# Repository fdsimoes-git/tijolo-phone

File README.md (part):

# Tijolo — dumbphone com ESP32-S3 e 4G

Celular "tijolinho" montado na **LILYGO T-A7670SA-S3-Standard**: ESP32-S3 + modem SIMCom A7670SA (4G Cat-1 + 2G) na mesma placa, com suporte para 18650, amplificador de áudio e conectores para alto-falante e microfone.

O firmware é o **TijoloOS**, feito por fases:

| Fase | O que entra | Situação |
|---|---|---|
| 1 | Modem: ligar, atender, SMS com acentos, USSD (saldo), toque — pelo Monitor Serial | pronta, testada na placa |
| 2 | Tela ILI9341 + teclado 3×4 (o 1 e o 3, segurados, fazem as vezes dos botões verde e vermelho): tela inicial, discador, chamadas, SMS recebidos, saldo, liga/desliga | pronta, testada na placa |
| 3a | Menu, escrever SMS pelo teclado (multitoque), caixa de mensagens na memória do Tijolo (ler, responder, encaminhar, apagar, reenviar) | pronta, testada na placa |
| 4 | **WhatsApp pela ponte**: um Android em casa, com o WhatsApp oficial, repassa as mensagens por SMS e devolve as respostas (app em [`ponte-android/`](ponte-android/README.md)) | pronta, falta testar na placa |
| 4 | **Montagem final**: PCB da frente encaixada nos pinos da LILYGO, sem fios soltos, e caixa impressa em 3D ([`montagem/`](montagem/README.md)) | desenhada e conferida no computador, já com as medidas das peças do Felipe; falta encomendar a PCB, imprimir a caixa e montar |
| 3b | Agenda de contatos (na memória do Tijolo), histórico de chamadas, despertador | depois |
| — | Modo roteador (compartilhar o 4G por Wi-Fi) | opcional |

O Monitor Serial continua aceitando todos os comandos da Fase 1.

## Peças

- LILYGO T-A7670SA-S3-Standard, versão **Without GPS** (modem A7670SA-LASE), com antena LTE, chip nano-SIM e uma 18650
- Alto-falante 3525 de 8 Ω, microfone de eletreto 9×7 mm e dois cabos JST SH 1.0 de 2 pinos (Fase 1)
- Tela TFT de 2,4" SPI com ILI9341 (240×320, sem touch)
- Teclado matricial 3×4 (12 teclas, 7 fios)
- Protoboard e jumpers (os 2 botões de pressão do kit Eletrogate são opcionais: sem eles, o 1 e o 3 seguradas fazem o papel deles)
- Para a montagem final: a PCB da frente (encomendada), duas barras fêmea de perna longa, fita dupla face de espuma e a caixa impressa em 3D (a lista completa está no guia de montagem; veja [Montagem final](#montagem-final-pcb-e-caixa))

## Montagem da Fase 1 (modem e áudio)

1. **Antena primeiro.** Nunca ligue o modem sem antena: transmitindo "no vazio", o amplificador de rádio dele pode queimar.
2. **Chip com a placa desligada.** Se o chip entrar com a placa ligada, o modem não o enxerga até reiniciar.
3. **Alto-falante → conector `SPEK`.** O alto-falante vem com um conector JST de 1,25 mm, que não serve: corte, emende os dois fios num cabo SH 1.0 (solda + termo-retrátil) e encaixe. A polaridade não importa para funcionar. Nunca ligue um fio do alto-falante ao GND: o amplificador (NS4150B) tem saída em ponte.
4. **Microfone → conector `MIC`.** A perninha ligada à carcaça metálica é o **negativo**. Encaixe o cabo SH 1.0 na placa, veja qual fio ficou do lado do **"+"** da serigrafia e solde nele a outra perninha.
5. **Bateria 18650** no suporte (polo + do lado marcado) e chave em **ON**. Na primeira vez a placa só liga pela bateria depois de ser conectada uma vez na USB **ESP-USB**: é o que destrava a proteção da bateria.

## Ligação da Fase 2 (tela e teclado)

Com a chave em OFF e sem USB. Se as barras de pinos vieram soltas, solde-as primeiro. O guia ilustrado (página "Fiação do Tijolo") mostra o mapa das duas barras; os nomes abaixo são os da serigrafia da placa.

**Não use IO1 nem IO41**: eles têm resistores de 5,1 kΩ até a alimentação da câmera, que fica desligada, e um botão ali leria "apertado" o tempo todo.

| Peça | Pino da peça | Pino da placa |
|---|---|---|
| Tela ILI9341 | VCC / GND | 3V3 / GND (os dois de baixo da barra do lado da chave) |
| | CS / RESET / DC | IO47 / IO9 / IO14 |
| | SDI (MOSI) / SCK | MOSI / SCK |
| | LED (luz de fundo) | IO36 |
| | SDO (MISO) | J1-15, MISO (IO13): opcional, recomendado (o Tijolo confere a tela por ele) |
| Teclado 3×4 | os 7 fios, **em qualquer ordem** | IO40, IO39, IO38, IO15, IO16, IO37, IO21 (seguidos, na barra do lado das USB) |
| Botão verde (opcional) | uma perninha no pino, a outra no GND | IO35, e `BOTAO_VERDE = 35` no `config.h` |
| Botão vermelho (opcional) | uma perninha no pino, a outra no GND | IO17, e `BOTAO_VERMELHO = 17` no `config.h` |

**Sem botões** (o padrão): segurar o **1** vale o verde e segurar o **3** vale o vermelho. Com os botões, os dois jeitos funcionam. Nos botões de 4 perninhas, use duas em diagonal. O GND dos botões pode vir do GND de cima da barra do lado das USB.

A tela divide o SPI com o cartão TF da placa (IO11/IO12); o firmware deixa o CS do cartão (IO10) em nível alto.

## Montagem final (PCB e caixa)

Para sair da protoboard: uma PCB encomendada (51,5 × 82,7 mm, 0,8 mm de espessura) encaixa direto nas duas barras de pinos da LILYGO e leva a tela, os botões verde e vermelho e a ligação do teclado 3×4, que entra inteiro. Não sobra fio solto: só os cabos do alto-falante e do microfone e a antena. Uma caixa impressa em 3D (56 × 162 × 36 mm) fecha tudo, com a antena colada por dentro, o alto-falante no alto, com o som saindo por fendas na frente, e o microfone embaixo.

- **O guia de montagem** ([página "Montagem do Tijolo"](https://claude.ai/artifact/CuJ8r7VZzr5Dn8WH7geubx), privada até ser compartilhada) tem as medidas das peças, o que comprar, como encomendar a PCB e imprimir a caixa, os 8 passos da montagem e a vista 3D.
- **Os arquivos prontos** estão em [`montagem/fabricar/`](montagem/fabricar/LEIA-ME.md): os Gerbers da PCB e os STL da caixa.
- **Os scripts** que geram a PCB, a caixa e o guia estão em [`montagem/`](montagem/README.md).
- **O firmware**: com `#define MONTAGEM_PLACA 2` no `config.h`, os botões passam a ser de verdade (verde no IO35, vermelho no IO21, que acorda a ESP32) e o teclado usa IO37, IO15, IO17, IO40, IO16, IO39 e IO38. A tela fica com os pinos para baixo, na rotação normal. Depois de gravar, ensine o teclado de novo (segure o 1 enquanto aparece "Ligando o modem…").

## Gravar e abrir o monitor

1. Abra a pasta `tijolo` no VS Code com o PlatformIO. Na primeira compilação ele baixa a LovyanGFX (a mesma do robô de mesa).
2. Placa na **ESP-USB**, com a bateria colocada (o modem puxa picos de ~2 A).
3. ✓ (Build), → (Upload) e o ícone da tomada (Monitor).
4. Se a gravação não começar: segure **BOOT**, aperte e solte **RST**, solte **BOOT** e mande gravar de novo.

## Primeira vez com a Fase 2

1. A tela mostra um tijolinho e "Ligando o modem…" (até 1 minuto).
2. **Configurar o teclado**: aperte as teclas que a tela pedir (1, 2, 3… 9, *, 0, #). O Tijolo descobre qual fio é linha e qual é coluna e guarda o mapa. No fim: "Teclado pronto!". Depois que o 1 e o 3 já foram aprendidos, segurar o 1 recomeça e segurar o 3 pula essa etapa.
3. Tela inicial: relógio (a hora vem da operadora), operadora, sinal e bateria.
4. Digite um número e segure o 1 (ligar). Segurar o 3 encerra.
5. Para desligar, segure o 3 na tela inicial por uns 2 segundos e confirme segurando o 1. Para ligar, segure o 3 por 1 segundo.

As bolinhas verde e vermelha no pé da tela mostram o 1 e o 3: a tecla 1 fica embaixo do canto esquerdo da tela, a 3 do direito.

Se o teclado for trocado ou religado em outra ordem: segure o 1 enquanto aparece "Ligando o modem…", ou digite `teclado aprender` no monitor.

## Mensagens (Fase 3)

**Menu**: na tela inicial sem novidades, segure o 1. Lá estão *Escrever mensagem*, *Continuar rascunho* (se você saiu no meio de uma), *Mensagens* (recebidas e enviadas) e *Rediscar*. O 2 e o 8 andam, o 5 (ou o 1 segurado) abre, o 3 segurado volta.

**Escrever** é pelo multitoque, como nos celulares antigos: toque a tecla até aparecer a letra; outra tecla, ou 1 segundo parado, confirma (a letra que ainda pode mudar fica sublinhada).

| Tecla | Letras |
|---|---|
| 1 | . , ? ! : ; ' " - ( ) @ / + = & % * # $ _ < > 1 |
| 2 | a b c á à â ã ç |
| 3 | d e f é ê |
| 4 | g h i í |
| 5 | j k l |
| 6 | m n o ó ô õ |
| 7 | p q r s |
| 8 | t u v ú |
| 9 | w x y z |
| 0 | espaço |
| * | troca o modo: **Abc** (maiúscula no começo de cada frase) → abc → ABC → 123 (o modo aparece no canto de cima) |
| # | apaga a última letra; segurado, a última palavra |

- Segurar uma tecla de letra dá o número dela. O 1 e o 3 não: segurados, eles são o verde e o vermelho (para eles, use o modo 123).
- Embaixo do texto aparece quanto já foi e quanto cabe: 160 letras por SMS sem acento; com qualquer acento ou ç, a mensagem inteira vai em UCS2 e cabem 70. Passando disso, ela vai em partes (até 6, `SMS_MAXIMO_DE_PARTES` no `config.h`), e cada parte é cobrada como um SMS.
- Segure o 1 para escolher o destinatário (digite o número; o # apaga) e segure o 1 de novo para enviar. A tela mostra "Enviando…" e depois "Mensagem enviada", ou o motivo da falha (sem rede, sem crédito...): segure o 1 para tentar de novo. A que não foi fica guardada, com um "!" na lista.
- Segurar o 3 sai do texto sem perder nada: ele vira o rascunho do menu. Escrevendo, a tela apaga mas não sai do lugar.

**Recebidas**: com o Tijolo na tela inicial, a mensagem nova abre sozinha; ela só conta como lida quando alguém toca numa tecla (se ninguém mexer, a tela apaga e ela continua nova). Na tela inicial fica o cartão das novidades: segure o 1 para ver (uma mensagem nova abre direto; várias, a lista) ou segure o 3 um pouco, menos de 1,6 s, para limpar a tela (as mensagens continuam marcadas como novas na lista).

**Lendo**: o 2 e o 8 rolam o texto, o 1 segurado responde, o 5 abre as opções (responder, ligar, encaminhar, apagar; numa que não foi enviada: tentar de novo, editar e enviar; numa do WhatsApp: silenciar e reativar a conversa) e o 3 segurado volta.

**Onde elas ficam**: na memória flash do Tijolo (a partição de dados de 3,4 MB, com o sistema de arquivos LittleFS), até 500 mensagens (`CAIXA_MAXIMO`); cheia, sai a mais antiga já lida. Depois de guardada, a mensagem sai do chip, que guarda poucas e, cheio, para de receber (`APAGAR_SMS_DO_CHIP` no `config.h`). Gravar um firmware novo não apaga as mensagens (só o "Erase Flash" do PlatformIO apagaria).

**Vindo da Fase 2**: no primeiro liga com a Fase 3, as mensagens que estavam no chip vão para a memória do Tijolo: as que você ainda não tinha visto entram como novas, as outras como lidas. O monitor conta quantas foram.

### Roteiro de teste da Fase 3 (uns 15 minutos)

1. **Gravar e ligar** com o monitor aberto. Na primeira vez aparece "Preparando a memória das mensagens" e depois a contagem: `SMS do chip para a memória do Tijolo: ...` e `Mensagens na memória do Tijolo: N`. `status` mostra a memória usada e `Chip: 0 de ... posições` (o chip esvaziou).
2. **Receber**: mande um SMS de outro celular com o Tijolo na tela inicial. Ele abre sozinho; toque o 8 (conta como lida) e segure o 3. No monitor, `lista` mostra a mensagem e `chip` diz que o chip está vazio.
3. **Nova sem ninguém ver**: mande outra e não toque em nada. A tela apaga em 30 s e volta para o início com o cartão "1 mensagem nova". Segure o 1: ela abre.
4. **Escrever**: tela inicial → segure o 1 (Menu) → 5 (Escrever mensagem). "Oi! Tudo bem?" é 666 444 1111 0 8, *espere 1 s* (o u está na mesma tecla do T), 88 3 666 0 22 33 6 111. Teste um acento (2222 = á), o * (modo) e o # (apaga; segurado, a palavra).
5. **Enviar**: segure o 1, digite o número do outro celular, segure o 1. "Enviando…" e depois "Mensagem enviada". Confira se chegou certo, com os acentos.
6. **Responder**: abra a mensagem recebida (Menu → Mensagens), segure o 1 (Responder), escreva e envie.
7. **Falha**: tire a antena (ou `radio desligar` no monitor), envie uma mensagem: aparece "Não foi possível enviar" e o motivo. Volte a antena (`radio ligar`), segure o 1 (Tentar de novo).
8. **Rascunho**: comece uma mensagem, segure o 3 (sai) e veja "Continuar rascunho" no Menu.
9. **Desligar e ligar** (segure o 3 na tela inicial): as mensagens continuam lá, nas mesmas condições (novas e lidas).

Se algo der errado, mande o que o monitor mostrou (e `lista` e `chip`).

## WhatsApp pela ponte (Fase 4)

O WhatsApp não roda no Tijolo. Então um **Android antigo fica em casa** (Android 6 ou mais novo, na tomada e no Wi-Fi, com um chip próprio) com o WhatsApp oficial e o app **Ponte do Tijolo**. Quando chega mensagem, a ponte lê a notificação e manda uma SMS para o Tijolo. Quando você responde no Tijolo, a ponte responde no WhatsApp pelo botão "Responder" da notificação. A instalação do Android está em [`ponte-android/README.md`](ponte-android/README.md): o app se instala **pelo computador**, com o cabo USB, porque no Brasil o Play Protect bloqueia esse tipo de app aberto pelo navegador ou pelo Drive. No Tijolo, basta dizer qual é o número do chip da ponte, com DDD:

```
ponte 11977776666
```

(ou `PONTE_WHATSAPP` no `config.h`).

- **Chegando**: a mensagem aparece como as outras, com **WhatsApp** em verde e o nome da pessoa ou do grupo. Na lista, a prévia começa com "WhatsApp ·".
- **Responder** é igual ao SMS. A tela "Enviar para" mostra o nome e "pelo WhatsApp". Um dígito ali troca a conversa por um número de telefone, e o # tira a conversa. Depois de enviar aparece "Enviada à ponte": quem põe a resposta no WhatsApp é a ponte, e se ela não conseguir, manda um aviso dizendo por quê.
- **Opções** (o 5, lendo): *Silenciar a conversa* e *Reativar a conversa* (para um grupo animado demais). Lendo um aviso da própria ponte: *Pausar o WhatsApp* e *Retomar o WhatsApp*. Esses pedidos vão por SMS à ponte e não ficam na caixa.
- O tamanho máximo conta o `WA#7xk ` que vai na frente da resposta.
- Só dá para **responder**, não para começar conversa: a ponte precisa da notificação daquela conversa. Entre o Android e o Tijolo, as mensagens vão por **SMS comum**: a operadora consegue ler, e cada SMS é cobrada.

Como o Tijolo reconhece: uma SMS **do número da ponte** que começa com `WA#7xk Nome` vira uma mensagem de "WA#7xk Nome". O 7 é o número da conversa na ponte e o `xk` é o código dela: se a ponte esquecer as conversas e o 7 virar outra pessoa, o código não bate e a resposta não vai para a pessoa errada. Esse endereço fica guardado na caixa e, na tela, vira só o nome. Responder a ele manda `WA#7xk texto` ao número da ponte. Os avisos da ponte (`WA!`, `WA?`) ficam como da **Ponte do WhatsApp**. Uma SMS da ponte fora desse formato fica como SMS comum.

### Roteiro de teste da Fase 4 (uns 40 minutos, depois de instalar a ponte)

Para os passos 8 a 11 você precisa de **dois** outros celulares com WhatsApp (A e B), ou de dois amigos dispostos a mandar mensagens.

1. **Gravar o firmware** e, no monitor, `ponte <número do chip do Android>`. `status` mostra a linha `WhatsApp:  ponte no +55...`.
2. No app da ponte, **Mandar uma SMS de teste ao Tijolo**. Chega uma mensagem da **Ponte do WhatsApp**.
3. `ponte lista` no monitor. A ponte responde "Conversas no WhatsApp: nenhuma conversa ainda" (ou a lista).
4. **Receber**: de outro celular, mande um WhatsApp para o seu número. Em uns 10 s chega no Tijolo, com "WhatsApp" em verde e o nome.
5. **Responder** pelo Tijolo e conferir no outro celular. Mande 3 mensagens seguidas do outro celular: elas chegam juntas, numa SMS.
6. **Emoji e foto**: mande 😂👍 e uma foto com legenda. Chegam `:D (ok)` e `[foto] legenda`.
7. **Grupo**: ligue *Repassar também os grupos* no app e mande algo num grupo. Chega com "Nome: texto". No Tijolo, *Silenciar a conversa*: a ponte confirma e o grupo para de chegar. *Reativar a conversa* volta.
8. **Duas conversas, sem notificação**: A e B mandam uma mensagem cada. No Android, **arraste as duas notificações para fora** (sem abrir o WhatsApp). Pelo Tijolo, responda a A, depois a B, depois a A **duas vezes seguidas**. Cada resposta tem de chegar na conversa certa, e todas têm de chegar.
9. **Depois de responder**: no app da ponte, a lista *Conversas* não pode ganhar uma conversa chamada "Você" (ou com o seu nome), e A e B continuam com os nomes certos.
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
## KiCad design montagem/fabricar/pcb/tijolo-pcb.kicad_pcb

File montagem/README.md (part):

# Montagem do Tijolo: PCB da frente e caixa 3D

O Tijolo fechado numa caixa impressa em 3D, sem fios soltos. Uma PCB encomendada encaixa direto nos pinos da LILYGO e leva
a tela, os botões verde e vermelho e a ligação do teclado. O teclado 3×4 entra inteiro, sem abrir. Sobram dois cabos (o do
alto-falante e o do microfone) e a antena.

- **Para montar**: o passo a passo está no [guia](https://claude.ai/artifact/CuJ8r7VZzr5Dn8WH7geubx), com as medidas das
  peças, o que comprar, como encomendar a PCB, como imprimir e a vista 3D.
- **Os arquivos prontos** estão em [`fabricar/`](fabricar/LEIA-ME.md): os Gerbers da PCB e os STL da caixa.
- **Esta pasta** tem os scripts que geram a PCB, a caixa e o guia: mudando uma medida em `projeto.py`, tudo se refaz igual.

## Como fica

- **A LILYGO vai de costas.** Os pinos dela estão soldados do lado da pilha e ficam assim. Os componentes olham para o fundo
  da caixa; a pilha e os pinos, para a frente. A ponta da ESP32 fica para baixo e os USB-C saem pela lateral direita. Dois
  pilares do fundo têm pino, que entra nos furos dela (Ø 2,55), e os outros dois recebem parafusos M2 × 5.
- **A PCB da frente** (51,5 × 82,7 mm, 0,8 mm) encaixa nos pinos com duas barras fêmea de perna longa e passa 0,6 mm acima
  da pilha. Nenhuma solda fica em cima da pilha: o script confere.
- **A tela** é soldada na PCB pelos próprios pinos, com os pinos para baixo, que é a posição normal dela (rotação 0). Os
  quatro pinos do toque que cairiam em cima da pilha são cortados; no lugar deles a PCB tem furos sem cobre, que escondem os
  toquinhos. A ponta de cima da tela apoia em duas torres do fundo, ao lado do alto-falante.
- **O teclado** fica colado na PCB com fita dupla face de espuma. A aba dos contatos se liga à PCB por 7 perninhas de fio.
  A frente cobre a aba de fora dele (a dos 4 furos): pela abertura só passa a parte alta, com as teclas.
- **O som** sai por três fendas na frente, acima da tela. O alto-falante fica em pé no alto da caixa, virado para a parede
  de cima, num canto fechado por uma parede; o som sobe por trás da ponta da tela.
- **O USB-C** de carregar aparece num rebaixo da lateral direita, por um furo do tamanho da ponta do cabo.
- **A frente sai inteira** (duas linguetas em cima, dois parafusos M2 × 8 embaixo) e o conjunto PCB + tela + teclado desencaixa
  dos pinos para trocar a pilha.
- **A chave liga/desliga** da LILYGO fica acessível por trás, numa fenda com ON e OFF gravados.

De trás para a frente (Z, em mm, a partir da face de fora do fundo):

| Z | O quê |
|---|---|
| 0 a 1,5 | o fundo da caixa |
| 1,5 a 5,0 | os componentes da LILYGO (o mais alto, o USB-C, tem 3,2; o conector SOLAR, de 6,25, tem de sair) |
| 5,0 a 6,6 | a placa da LILYGO |
| 6,6 a 26,6 | a pilha 18650 no suporte (20,0 mm, medidos; pelo modelo 3D eram de 18,1 a 18,9) |
| 27,2 a 28,0 | a PCB da frente |
| 30,5 a 34,8 | a tela, apoiada no plástico da barra de pinos dela |
| 35,8 | a face da frente da caixa |
| 39,7 | o topo das teclas (saem 3,9 mm da caixa) |

A caixa tem 56,0 × 161,8 × 35,8 mm. Quem manda na espessura é a pilha: LILYGO mais pilha somam 21,6 mm e a
tela soma 8. A PCB tira 2,3 mm em relação ao desenho anterior, de placa ilhada (38,2 mm), e acaba com os 19 fios.
Para afinar mais, só trocando a 18650 por uma bateria chata (uns 26 mm), o que pede dessoldar o suporte.

## Os arquivos

| Arquivo | O que faz |
|---|---|
| `projeto.py` | Todas as medidas num lugar só: a LILYGO, a tela, o teclado, as alturas (Z), a PCB, a caixa, o alto-falante e o microfone. `MEDIDAS` lista as que só dá para confirmar com a peça na mão, e a faixa que serve. `python3 projeto.py` mostra um resumo. |
| `lilygo_pecas.json` | As caixas das peças da LILYGO, tiradas do modelo 3D oficial (T-A7670X-S3-Standard.step, de 26/08/2026): onde está cada peça e a altura dela, dos dois lados da placa. |
| `placa/placa.py` | A PCB (KiCad 7, pelo `pcbnew`): põe as peças, traça as trilhas, enche o GND, roda o teste de regras e gera os Gerbers para a JLCPCB, a lista de peças e as imagens. Para se alguma solda ficar em cima da pilha. |
| `placa/roteador.py` | O traçador de trilhas: grade de 0,2 mm, 2 camadas, vias, trechos a 0°, 45° e 90°. |
| `caixa/caixa.py` | A caixa (CadQuery): o fundo, a frente e os dois botões, já virados do jeito de imprimir, e versões leves para a vista 3D do guia. No fim, confere se cada peça é um sólido só e se alguma peça de dentro bate na caixa ou em outra peça. |
| `guia.py` | O guia: `saida/guia/index.html`, os desenhos da PCB e `saida/guia/3d/pecas.json` (as peças da vista 3D). |
| `empacotar.py` | Copia para `fabricar/` o que vai para a fábrica de placas e para a gráfica 3D, e faz o zip da caixa. |

O que os scripts geram sai em `saida/` (fora do git). O que vale guardar vai para `fabricar/` (no git).

## Como gerar

Precisa do Python 3.10 ou mais novo com `numpy`, `shapely` e `Pillow`, do KiCad 7 (para a PCB) e do CadQuery 2.x (para a
caixa). Da pasta `montagem/`:

```
python3 projeto.py           # o resumo das medidas
python3 placa/placa.py       # a PCB (uns 20 segundos): o KiCad, os Gerbers e o teste de regras
python3 caixa/caixa.py       # a caixa (menos de 1 minuto) e a conferência
python3 guia.py              # o guia
python3 empacotar.py         # a pasta fabricar/ e o zip da caixa
```

`caixa/caixa.py fundo`, `frente`, `botoes`, `visual`, `folgas` ou `conferir` faz só aquela parte. `folgas` lista as menores
distâncias entre a caixa e as peças.

## As medidas e de onde vieram

As peças do Felipe foram medidas em 24/11/2026 (na tabela, "medido"). Quem montar com peças de outra medida troca o valor
em `projeto.py` e gera tudo de novo.

| Peça | Medidas usadas | Fonte |
|---|---|---|
| LILYGO | placa 33,07 × 110,54 × 1,6 mm; duas barras de 16 pinos a 30,45 mm uma da outra, com o plástico do lado da pilha; 4 furos de Ø 2,55; suporte da pilha com 15 mm | modelo 3D oficial, desenho com cotas (DXF) e foto do lado da pilha, do [repositório da LILYGO](https://github.com/Xinyuan-LilyGO/LilyGo-Modem-Series/tree/main/dimensions/Standard) |
| Pilha | topo a 20,0 mm da face da placa, mais 0,6 mm de folga até a PCB | medido (pelo modelo 3D eram de 18,1 a 18,9) |
| Tela | plaquinha 42,72 × 77,18 mm; pinos a 2,00 mm da borda, o 1 (VCC) a 4,85 mm da esquerda; vidro de 10,41 a 70,67 mm; imagem 36,72 × 48,96 mm; soquete do cartão SD atrás, com 3,0 mm de altura | desenho do fabricante ([LCDWiki, MSP2401_Size.pdf](https://www.lcdwiki.com/res/MSP2402/MSP2401_Size.pdf), V1.0 de 15/04/2024) |
| Teclado | corpo 51,2 × 63,7 mm; aba dos contatos 36,2 × 5,3 mm com 9 furos a 2,54 mm; espessura 10,2 mm | corpo e espessura medidos; a aba, pela foto com cotas do anúncio e pela ficha da [Adafruit 3845](https://www.adafruit.com/product/3845) (o mesmo teclado) |
| Alto-falante | 35,3 × 25 × 6,0 mm (a calha tem 35,7 × 6,4) | medido |
| Teclado: aba de fora e parte alta | aba de fora com 3,8 mm de altura; parte alta (a das teclas) com 45,7 × 56,4 mm em cima, a 3,45 mm da borda de cima do corpo | altura e tamanho medidos; a posição, pela foto do anúncio: **conferir** |
| Microfone | Ø 9,7 × 6,7 mm | nome da peça (9767) |
| Chaves tácteis | 6 × 6 mm, 4,8 mm de altura (serve de 4,5 a 5,0) | medido |
| Barras fêmea | perna de 10,9 mm (o mínimo é 10,9: a ponta passa 0,5 mm da PCB); corpo de 8,5 mm | perna medida; o corpo é o tamanho comum |

## A PCB

Duas camadas, 0,8 mm. Na face de trás (a que olha para a pilha) ficam as duas barras fêmea e os capacitores da tela; na da
frente, a tela, as duas chaves tácteis e o teclado.

| Na PCB | Liga em | Pino da ESP32 |
|---|---|---|
| Tela: VCC, GND | J1-1 e J2-3 (3V3), GND | — |
| Tela: CS, RESET, DC | J1-4, J1-6, J1-5 | IO47, IO9, IO14 |
| Tela: SDI (MOSI), SCK, LED, SDO (MISO) | J1-13, J1-14, J1-7, J1-15 | IO11, IO12, IO36, IO13 |
| Aba do teclado, furos 2 a 8 | J2-13, J2-11, J1-10, J2-8, J2-12, J2-9, J2-10 | IO37, IO15, IO17, IO40, IO16, IO39, IO38 |
| Botão verde, botão vermelho | J1-8, J2-14 | IO35, IO21 |
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
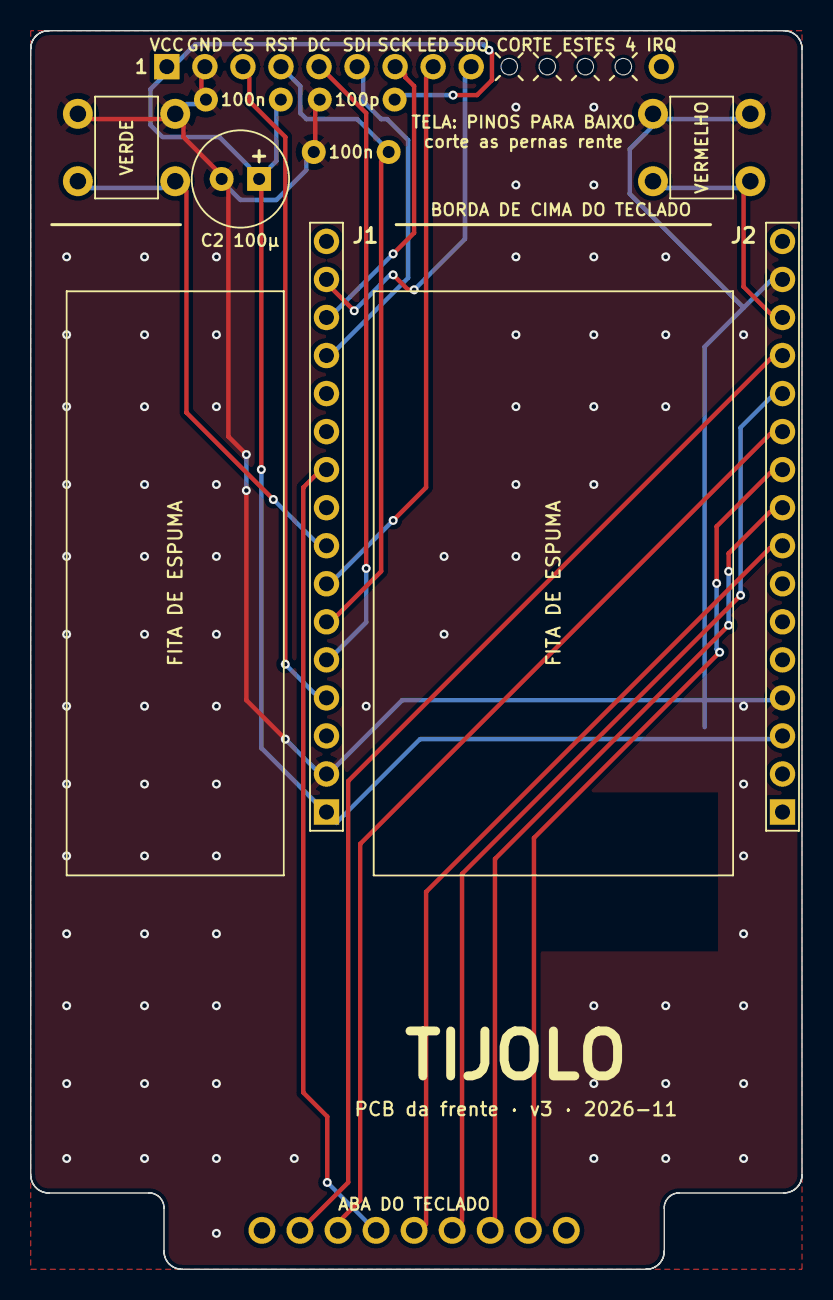
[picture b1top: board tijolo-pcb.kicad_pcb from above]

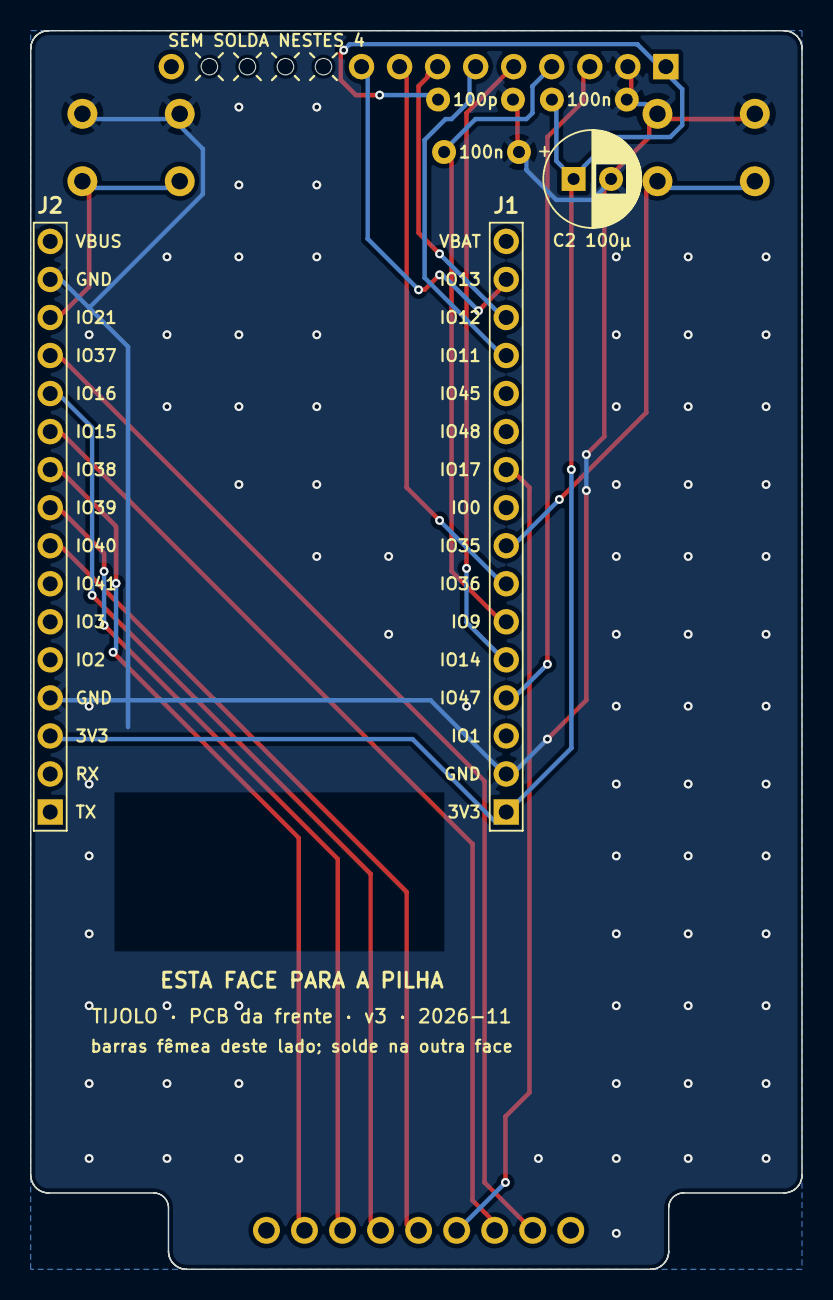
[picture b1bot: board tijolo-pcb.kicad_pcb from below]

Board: 2 copper layers, 51.5 x 82.7 mm, 10 parts (6 on the bottom side), 18 nets.

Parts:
C1, C5: 100 nF; C_Disc_D5.0mm_W2.5mm_P5.00mm
C2: 100 µF; CP_Radial_D6.3mm_P2.50mm
C4: 100 pF; C_Disc_D5.0mm_W2.5mm_P5.00mm
J1, J2: perna de 10,9 mm ou mais; PinSocket_1x16_P2.54mm_Vertical
SW1, SW2: 4,8 mm de altura; SW_PUSH_6mm
TECLADO: teclado 3×4 (a aba)
TELA: tela ILI9341 2,4"

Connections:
3V3: C1.1, C2.1, C4.1, J1.1, J2.3, TELA.1
GND: C1.2, C2.2, C4.2, C5.2, J1.2, J2.4, J2.15, SW1.1, SW2.1, TELA.2
IO9: C5.1, J1.6, TELA.4
IO11: J1.13, TELA.6
IO12: J1.14, TELA.7
IO13: J1.15, TELA.9
IO14: J1.5, TELA.5
IO15: J2.11, TECLADO.3
IO16: J2.12, TECLADO.6
IO17: J1.10, TECLADO.4
IO21: J2.14, SW2.2
IO35: J1.8, SW1.2
IO36: J1.7, TELA.8
IO37: J2.13, TECLADO.2
IO38: J2.10, TECLADO.8
IO39: J2.9, TECLADO.7
IO40: J2.8, TECLADO.5
IO47: J1.4, TELA.3

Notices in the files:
README.md:
Letras: fonte Inter, (c) 2016 The Inter Project Authors, SIL Open Font License 1.1 (`lib/Tela/LICENCA-Inter.txt`). Tela: LovyanGFX (MIT/BSD).
